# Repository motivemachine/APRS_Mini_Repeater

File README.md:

### Project goal
The goal of this in-progress project is to create a simple APRS position reporter and repeater. This will serve as a stepping stone toward my full APRS text-message radio, while providing a useful purpose later as an easy to deploy repeater for better coverage between groups of hikers, bikers, or road-trippers. It will be able to use smart-beaconing to know when to update it's position, and if repeater mode is turned on, repeat any packets heard that are not addressed to it.

This PCB uses the nano-modem board I developed here: [APRS Nanomodem]https://gitlab.com/motivemachine/aprs-nanomodem
Which is based on the Arduino TNC circuit and library developed by Mark Qvist here: [unsigned.io](https://unsigned.io/micromodem/)

### Project status
PCB is complete and undergoing testing. Board is designed in Kicad 5.1, gerbers will be available soon. 

 Writing the code has just started. I'll get the smart beaconing working first, then start in on the repeater functions and [hopefully] get it to conform with the APRS repeater WIDEn-N standard:
[APRS 101](http://www.aprs.org/doc/APRS101.PDF)

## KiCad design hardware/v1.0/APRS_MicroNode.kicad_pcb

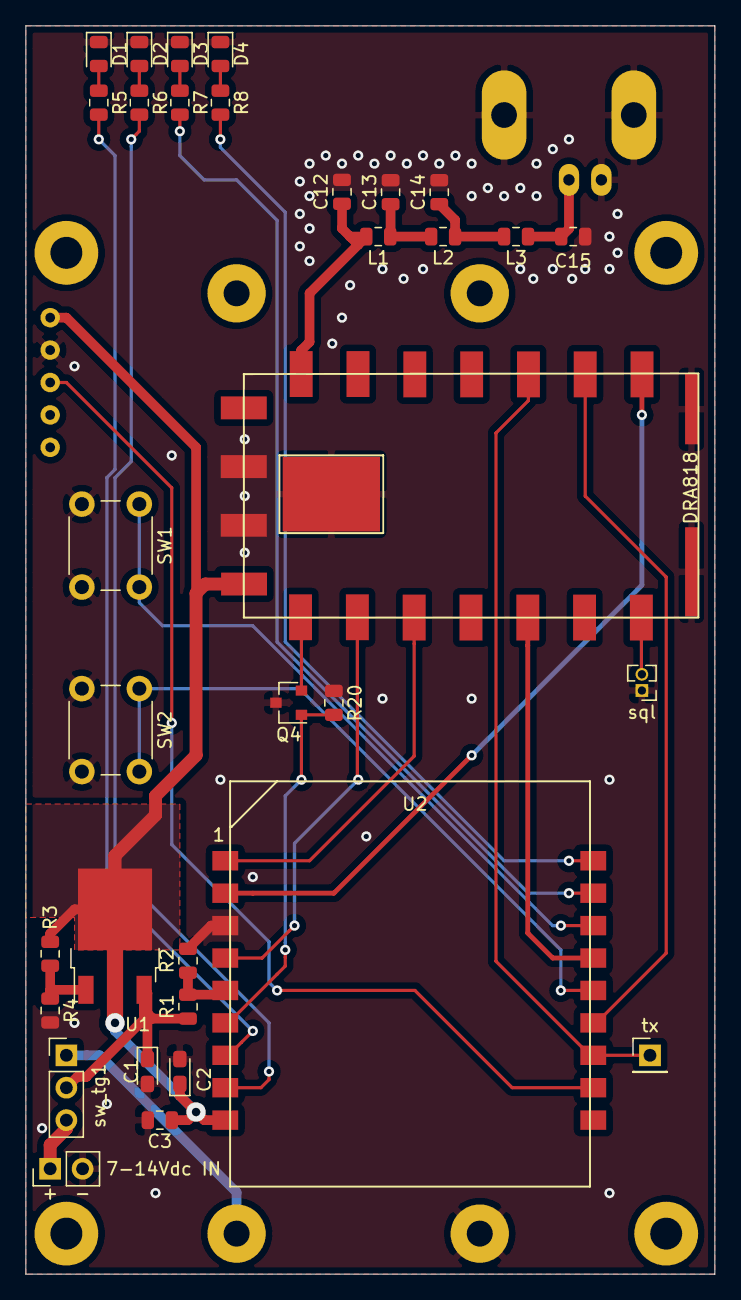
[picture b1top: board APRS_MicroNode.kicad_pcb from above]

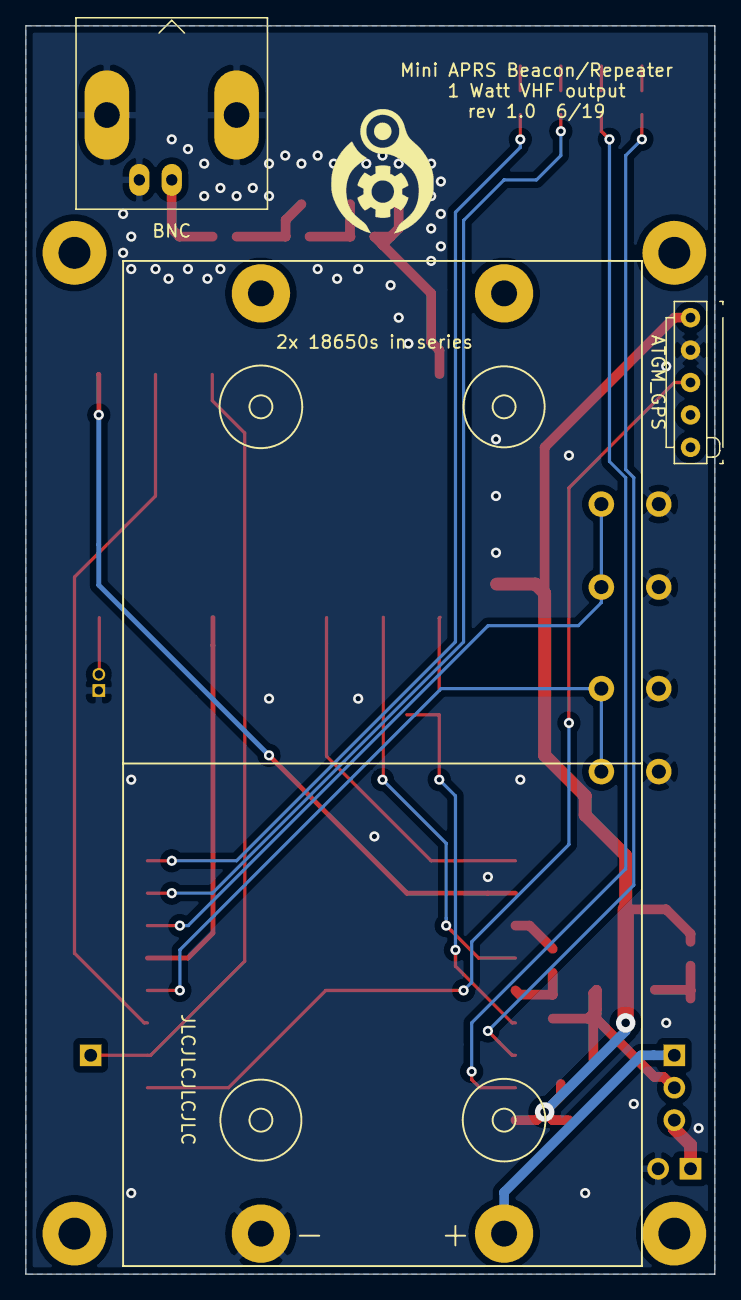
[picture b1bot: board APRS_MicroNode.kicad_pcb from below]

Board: 2 copper layers, 54.0 x 97.8 mm, 40 parts (3 on the bottom side), 32 nets.

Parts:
2x 18650s in series: Series_2_batteries; 18650_Double_Holder
ATGM_GPS: ATGM336_Gps; ATGM336_GPS_Vertical
BNC: Conn_Coaxial; BNC_pcbmount_h
C1: 10uf; CP_EIA-2012-12_Kemet-R_Pad1.30x1.05mm_HandSolder
C2: 22uf; CP_EIA-2012-12_Kemet-R_Pad1.30x1.05mm_HandSolder
C3: 1uf; C_0805_2012Metric
C12, C13, C14, C15: C; C_0805_2012Metric
D1, D2, D3, D4: LED; LED_0805_2012Metric
DRA818: DRA818
H1, H2, H3, H4: MountingHole; MountingHole_2.5mm_Pad
J1: Barrel_Jack; PinHeader_1x02_P2.54mm_Vertical
L1, L2, L3: L; L_0805_2012Metric
Q4: Q_PNP_BEC; SOT-23
R1, R2, R5, R6, R7, R8: R; R_0805_2012Metric
R3: 470; R_0805_2012Metric
R4: 1k2; R_0805_2012Metric
R20: 100k; R_0805_2012Metric
SW1, SW2: SW_Push; SW_PUSH_6mm_H5mm
U1: AZ1117-ADJ; TO-252-3_TabPin2
U2: NanoModem; Nanomodem_TNC_2.0
sql: sq_test; PinHeader_1x02_P1.27mm_Vertical
sw_tg1: SPDT; PinHeader_1x03_P2.54mm_Vertical
tx: tx; PinHeader_1x01_P2.54mm_Vertical

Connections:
/chrgLvl: R1.2, R2.1, U2.5
/dra_audioin: DRA818.18, U2.2
/dra_audioout: DRA818.3, U2.15
/gps_tx: ATGM_GPS.3, U2.11
/hilo: Q4.1, R20.2, U2.6
/led1: R7.2, U2.17
/led2: R8.2, U2.18
/pd: DRA818.6, U2.4
/ptt: DRA818.5, U2.1
/radio/squelch: DRA818.1, sql.2
/rxled: R5.2, U2.7
/sw1: SW2.1, U2.14
/sw2: SW1.1, U2.16
/tnc_rx: DRA818.17, U2.13
/tnc_tx: DRA818.16, U2.12, tx.1
/txled: R6.2, U2.8
GND: 2x 18650s in series.4, ATGM_GPS.2, BNC.2, C1.2, C2.2, C3.2, C12.2, C13.2, C14.2, C15.2, D1.1, D2.1, D3.1, D4.1, DRA818.9, DRA818.10, J1.2, Q4.3, R2.2, R4.2, R20.1, SW1.2, SW2.2, U2.3, sql.1
unnamed: 2x 18650s in series.1, sw_tg1.2
unnamed: 2x 18650s in series.2, 2x 18650s in series.3
unnamed: C1.1, R1.1, U1.3, sw_tg1.1
unnamed: C12.1, DRA818.12, L1.2
unnamed: C13.1, L1.1, L2.2
unnamed: C14.1, L2.1, L3.2
unnamed: BNC.1, C15.1, L3.1
unnamed: D1.2, R5.1
unnamed: D2.2, R6.1
unnamed: D3.2, R7.1
unnamed: D4.2, R8.1
unnamed: J1.1, sw_tg1.3
unnamed: DRA818.7, Q4.2
unnamed: R3.2, R4.1, U1.1
VCC: ATGM_GPS.1, C2.1, C3.1, DRA818.8, R3.1, U1.2, U2.9

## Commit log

2019-12-18 upload PCB design
2019-12-18 upload pdf schematic
